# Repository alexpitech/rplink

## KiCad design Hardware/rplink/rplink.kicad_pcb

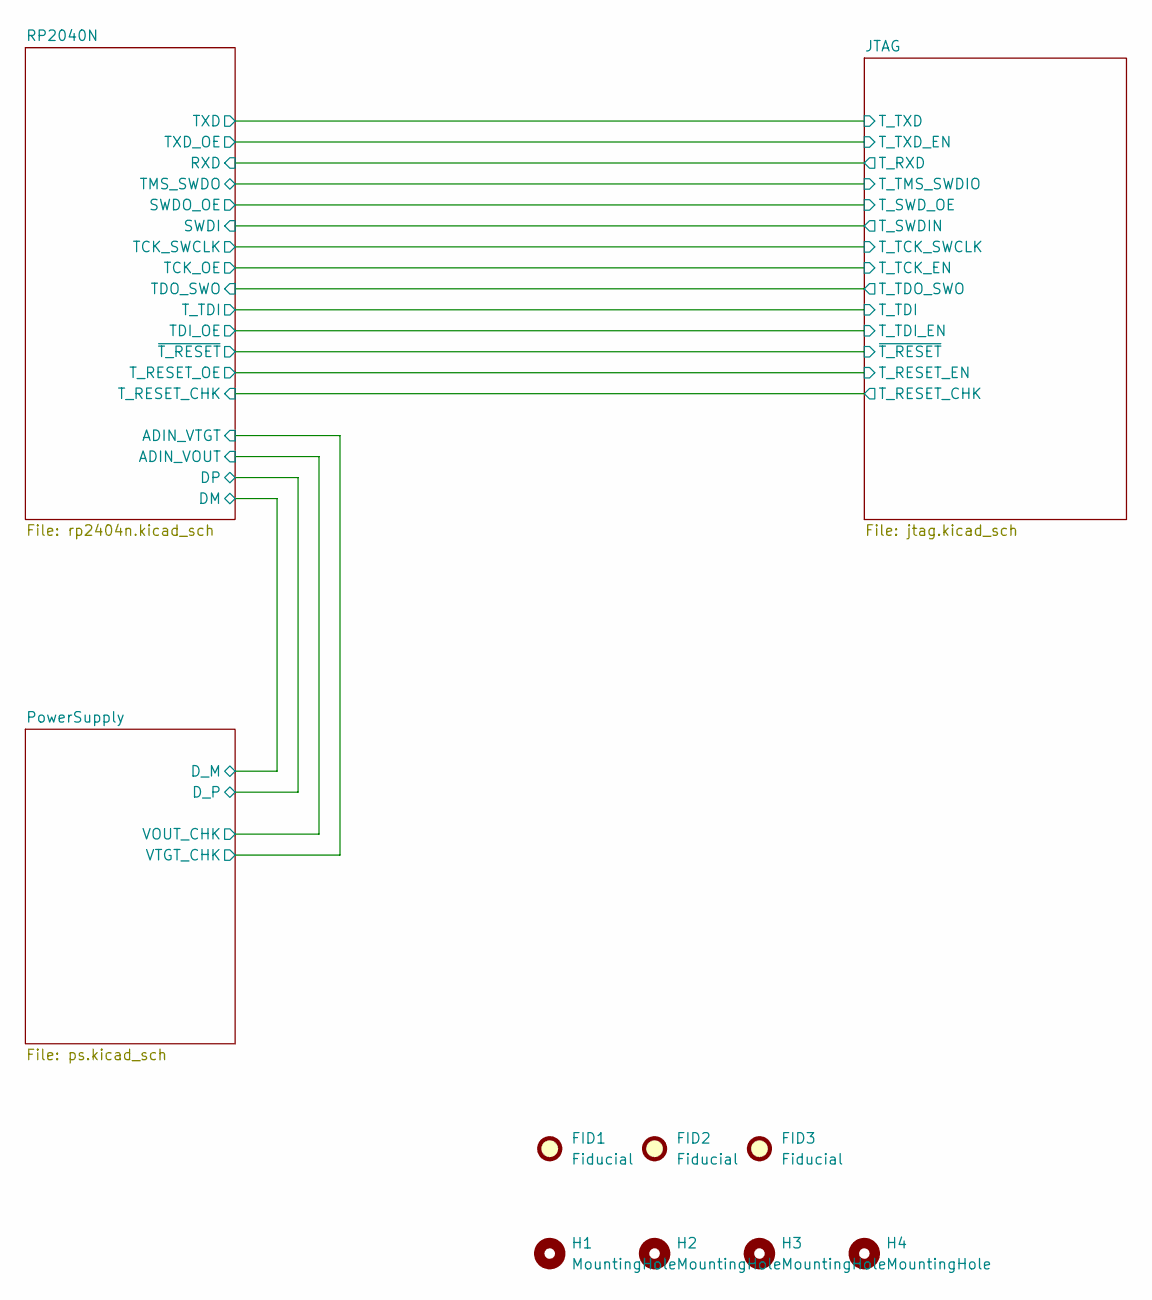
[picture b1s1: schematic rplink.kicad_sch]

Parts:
FID1, FID2, FID3: Fiducial; Fiducial_0.5mm_Mask1.5mm
H1, H2, H3, H4: MountingHole; MountingHole_3.2mm_M3

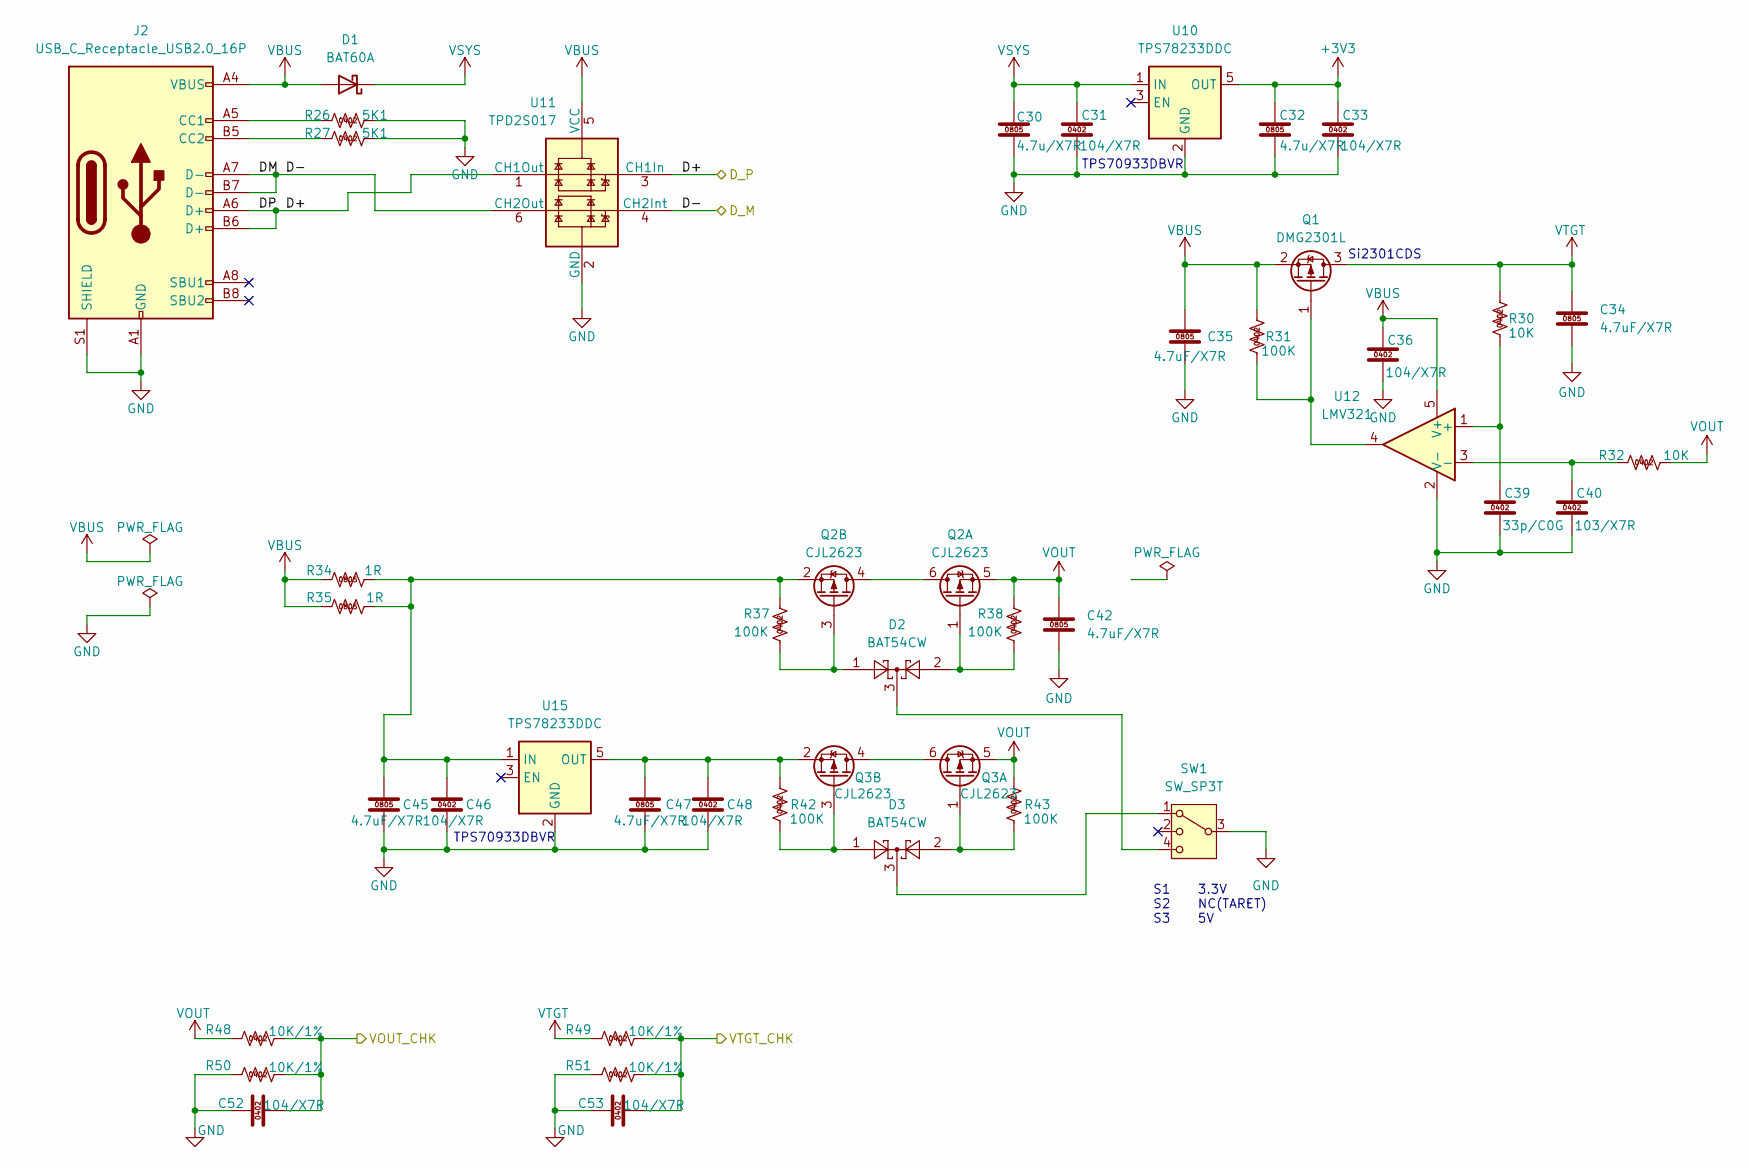
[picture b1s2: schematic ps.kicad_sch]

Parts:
C30, C32: 4.7u/X7R; C_0805_2012Metric
C31, C33, C36, C46, C48, C52, C53: 104/X7R; C_0402_1005Metric
C34, C35, C42, C45, C47: 4.7uF/X7R; C_0805_2012Metric
C39: 33p/C0G; C_0402_1005Metric
C40: 103/X7R; C_0402_1005Metric
D1: BAT60A; D_SOD-323
D2, D3: BAT54CW; SOT-323_SC-70
J2: USB_C_Receptacle_USB2.0_16P
Q1: DMG2301L; SOT-23
Q2, Q3: CJL2623; SOT-23-6
R26, R27: 5K1; R_0402_1005Metric
R30, R32: 10K; R_0402_1005Metric
R31, R37, R38, R42, R43: 100K; R_0402_1005Metric
R34, R35: 1R; R_0805_2012Metric
R48, R49, R50, R51: 10K/1%; R_0402_1005Metric
SW1: SW_SP3T; SW_SP3T_PCM13
U10, U15: TPS78233DDC; SOT-23-5
U11: TPD2S017; SOT-23-6
U12: LMV321; SOT-23-5

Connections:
+3V3: C32.1, C33.1, U10.5 (OUT); also elsewhere on the board
/PowerSupply/D+: J2.A6 (D+), J2.B6 (D+), U11.1 (CH1Out), U11.3 (CH1In); also elsewhere on the board
/PowerSupply/D-: J2.A7 (D-), J2.B7 (D-), U11.4 (CH2Int), U11.6 (CH2Out); also elsewhere on the board
/PowerSupply/VOUT_CHK: C52.2, R48.2, R50.2; also elsewhere on the board
/PowerSupply/VTGT_CHK: C53.2, R49.2, R51.2; also elsewhere on the board
GND: C30.2, C31.2, C32.2, C33.2, C34.2, C35.2, C36.2, C39.2, C40.2, C42.2, C45.2, C46.2, C47.2, C48.2, C52.1, C53.1, J2.A1 (GND), J2.A12 (GND), J2.B1 (GND), J2.B12 (GND), J2.S1 (SHIELD), R26.2, R27.2, R50.1, R51.1, SW1.3, U10.2 (GND), U10.4 (GND), U11.2 (GND), U12.2 (V-), U15.2 (GND), U15.4 (GND); also elsewhere on the board
unnamed: D2.3, SW1.4
unnamed: D3.3, SW1.1
unnamed: J2.A5 (CC1), R26.1
unnamed: J2.B5 (CC2), R27.1
unnamed: Q1.1 (G), R31.1, U12.4
unnamed: Q2.4 (D), Q2.6 (D)
unnamed: D2.2, Q2.1 (G), R38.1
unnamed: D2.1, Q2.3 (G), R37.1
unnamed: C45.1, C46.1, Q2.2 (S), R34.2, R35.2, R37.2, U15.1 (IN)
unnamed: Q3.4 (D), Q3.6 (D)
unnamed: D3.2, Q3.1 (G), R43.1
unnamed: D3.1, Q3.3 (G), R42.1
unnamed: C47.1, C48.1, Q3.2 (S), R42.2, U15.5 (OUT)
unnamed: C39.1, R30.1, U12.1 (+)
unnamed: C40.1, R32.1, U12.3 (-)
VBUS: C35.1, C36.1, D1.2 (A), J2.A4 (VBUS), J2.A9 (VBUS), J2.B4 (VBUS), J2.B9 (VBUS), Q1.2 (S), R31.2, R34.1, R35.1, U11.5 (VCC), U12.5 (V+)
VOUT: C42.1, Q2.5 (S), Q3.5 (S), R32.2, R38.2, R43.2, R48.1; also elsewhere on the board
VSYS: C30.1, C31.1, D1.1 (K), U10.1 (IN)
VTGT: C34.1, Q1.3 (D), R30.2, R49.1; also elsewhere on the board

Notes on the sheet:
Si2301CDS
TPS70933DBVR
S1 3.3V S2 NC(TARET) S3 5V

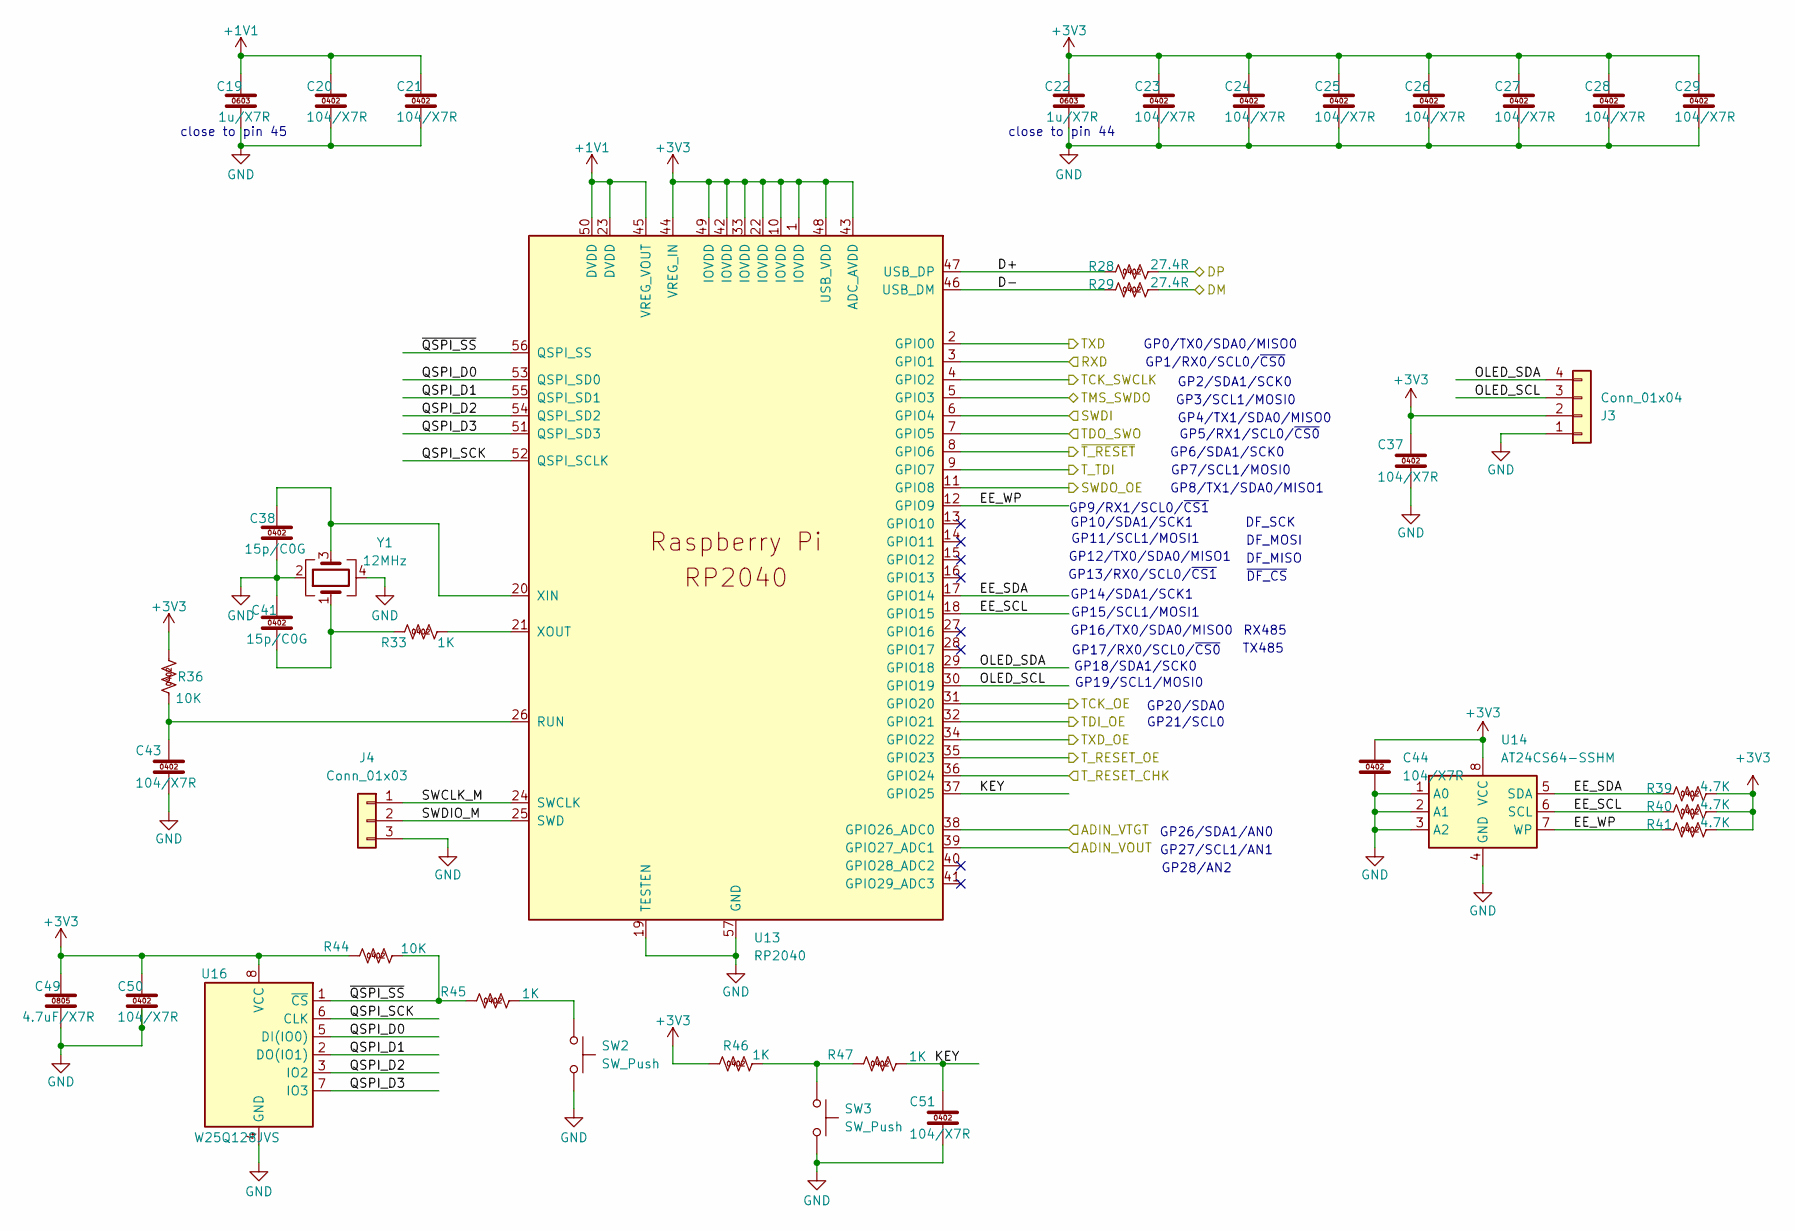
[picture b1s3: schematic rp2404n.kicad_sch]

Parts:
C19, C22: 1u/X7R; C_0603_1608Metric
C20, C21, C23, C24, C25, C26, C27, C28, C29, C37, C43, C44, C50, C51: 104/X7R; C_0402_1005Metric
C38, C41: 15p/C0G; C_0402_1005Metric
C49: 4.7uF/X7R; C_0805_2012Metric
J3: Conn_01x04; PinHeader_1x04_P2.54mm_Vertical
J4: Conn_01x03; PinHeader_1x03_P2.54mm_Vertical
R28, R29: 27.4R; R_0402_1005Metric
R33, R45, R46, R47: 1K; R_0402_1005Metric
R36, R44: 10K; R_0402_1005Metric
R39, R40, R41: 4.7K; R_0402_1005Metric
SW2: SW_Push; SW_Push_1P1T-MP_NO_Horizontal_Alps_SKRTLAE010
SW3: SW_Push; SW_Push_1P1T_NO_CK_KMR2
U13: RP2040; RP2040-QFN-56
U14: AT24CS64-SSHM; SOIC-8_3.9x4.9mm_P1.27mm
U16: W25Q128JVS; SOIC-8_5.23x5.23mm_P1.27mm
Y1: 12MHz; Crystal_SMD_WE_CFPX-180-4Pin_3.2x2.5mm

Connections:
+1V1: C19.1, C20.1, C21.1, U13.23 (DVDD), U13.45 (VREG_VOUT), U13.50 (DVDD)
+3V3: C22.1, C23.1, C24.1, C25.1, C26.1, C27.1, C28.1, C29.1, C37.1, C44.1, C49.1, C50.1, J3.2, R36.2, R39.2, R40.2, R41.2, R44.1, R46.1, U13.1 (IOVDD), U13.10 (IOVDD), U13.22 (IOVDD), U13.33 (IOVDD), U13.42 (IOVDD), U13.43 (ADC_AVDD), U13.44 (VREG_IN), U13.48 (USB_VDD), U13.49 (IOVDD), U14.8 (VCC), U16.8 (VCC); also elsewhere on the board
/JTAG/T_RESET_CHK: U13.36 (GPIO24); also elsewhere on the board
/JTAG/T_RESET_EN: U13.35 (GPIO23); also elsewhere on the board
/JTAG/T_RXD: U13.3 (GPIO1); also elsewhere on the board
/JTAG/T_SWDIN: U13.6 (GPIO4); also elsewhere on the board
/JTAG/T_SWD_OE: U13.11 (GPIO8); also elsewhere on the board
/JTAG/T_TCK_EN: U13.31 (GPIO20); also elsewhere on the board
/JTAG/T_TCK_SWCLK: U13.4 (GPIO2); also elsewhere on the board
/JTAG/T_TDI: U13.9 (GPIO7); also elsewhere on the board
/JTAG/T_TDI_EN: U13.32 (GPIO21); also elsewhere on the board
/JTAG/T_TDO_SWO: U13.7 (GPIO5); also elsewhere on the board
/JTAG/T_TMS_SWDIO: U13.5 (GPIO3); also elsewhere on the board
/JTAG/T_TXD: U13.2 (GPIO0); also elsewhere on the board
/JTAG/T_TXD_EN: U13.34 (GPIO22); also elsewhere on the board
/JTAG/~T_RESET: U13.8 (GPIO6); also elsewhere on the board
/PowerSupply/D+: R28.2; also elsewhere on the board
/PowerSupply/D-: R29.2; also elsewhere on the board
/PowerSupply/VOUT_CHK: U13.39 (GPIO27_ADC1); also elsewhere on the board
/PowerSupply/VTGT_CHK: U13.38 (GPIO26_ADC0); also elsewhere on the board
/RP2040N/D+: R28.1, U13.47 (USB_DP)
/RP2040N/D-: R29.1, U13.46 (USB_DM)
/RP2040N/EE_SCL: R40.1, U13.18 (GPIO15), U14.6 (SCL)
/RP2040N/EE_SDA: R39.1, U13.17 (GPIO14), U14.5 (SDA)
/RP2040N/EE_WP: R41.1, U13.12 (GPIO9), U14.7 (WP)
/RP2040N/KEY: C51.1, R47.2, U13.37 (GPIO25)
/RP2040N/OLED_SCL: J3.3, U13.30 (GPIO19)
/RP2040N/OLED_SDA: J3.4, U13.29 (GPIO18)
/RP2040N/QSPI_D0: U13.53 (QSPI_SD0), U16.5 (DI(IO0))
/RP2040N/QSPI_D1: U13.55 (QSPI_SD1), U16.2 (DO(IO1))
/RP2040N/QSPI_D2: U13.54 (QSPI_SD2), U16.3 (IO2)
/RP2040N/QSPI_D3: U13.51 (QSPI_SD3), U16.7 (IO3)
/RP2040N/QSPI_SCK: U13.52 (QSPI_SCLK), U16.6 (CLK)
/RP2040N/SWCLK_M: J4.1, U13.24 (SWCLK)
/RP2040N/SWDIO_M: J4.2, U13.25 (SWD)
/RP2040N/~QSPI_SS: R44.2, R45.1, U13.56 (QSPI_SS), U16.1 (~CS)
GND: C19.2, C20.2, C21.2, C22.2, C23.2, C24.2, C25.2, C26.2, C27.2, C28.2, C29.2, C37.2, C38.1, C41.2, C43.2, C44.2, C49.2, C50.2, C51.2, J3.1, J4.3, SW2.2, SW3.2, U13.19 (TESTEN), U13.57 (GND), U14.1 (A0), U14.2 (A1), U14.3 (A2), U14.4 (GND), U16.4 (GND), Y1.2, Y1.4; also elsewhere on the board
unnamed: C41.1, R33.1, Y1.1
unnamed: R45.2, SW2.1
unnamed: R46.2, R47.1, SW3.1
unnamed: C43.1, R36.1, U13.26 (RUN)
unnamed: C38.2, U13.20 (XIN), Y1.3
unnamed: R33.2, U13.21 (XOUT)

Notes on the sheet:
GP14/SDA1/SCK1
GP26/SDA1/AN0
TX485
~{DF_CS}
GP8/TX1/SDA0/MISO1
GP27/SCL1/AN1
GP0/TX0/SDA0/MISO0
GP15/SCL1/MOSI1
GP13/RX0/SCL0/~{CS1}
GP3/SCL1/MOSI0
DF_SCK
GP4/TX1/SDA0/MISO0
GP12/TX0/SDA0/MISO1
GP16/TX0/SDA0/MISO0
GP19/SCL1/MOSI0
RX485
GP18/SDA1/SCK0
close to pin 44
DF_MISO
GP1/RX0/SCL0/~{CS0}
GP2/SDA1/SCK0
close to pin 45
GP5/RX1/SCL0/~{CS0}
GP10/SDA1/SCK1
GP7/SCL1/MOSI0
GP6/SDA1/SCK0
GP20/SDA0
GP11/SCL1/MOSI1
DF_MOSI
GP17/RX0/SCL0/~{CS0}
GP9/RX1/SCL0/~{CS1}
GP28/AN2
GP21/SCL0

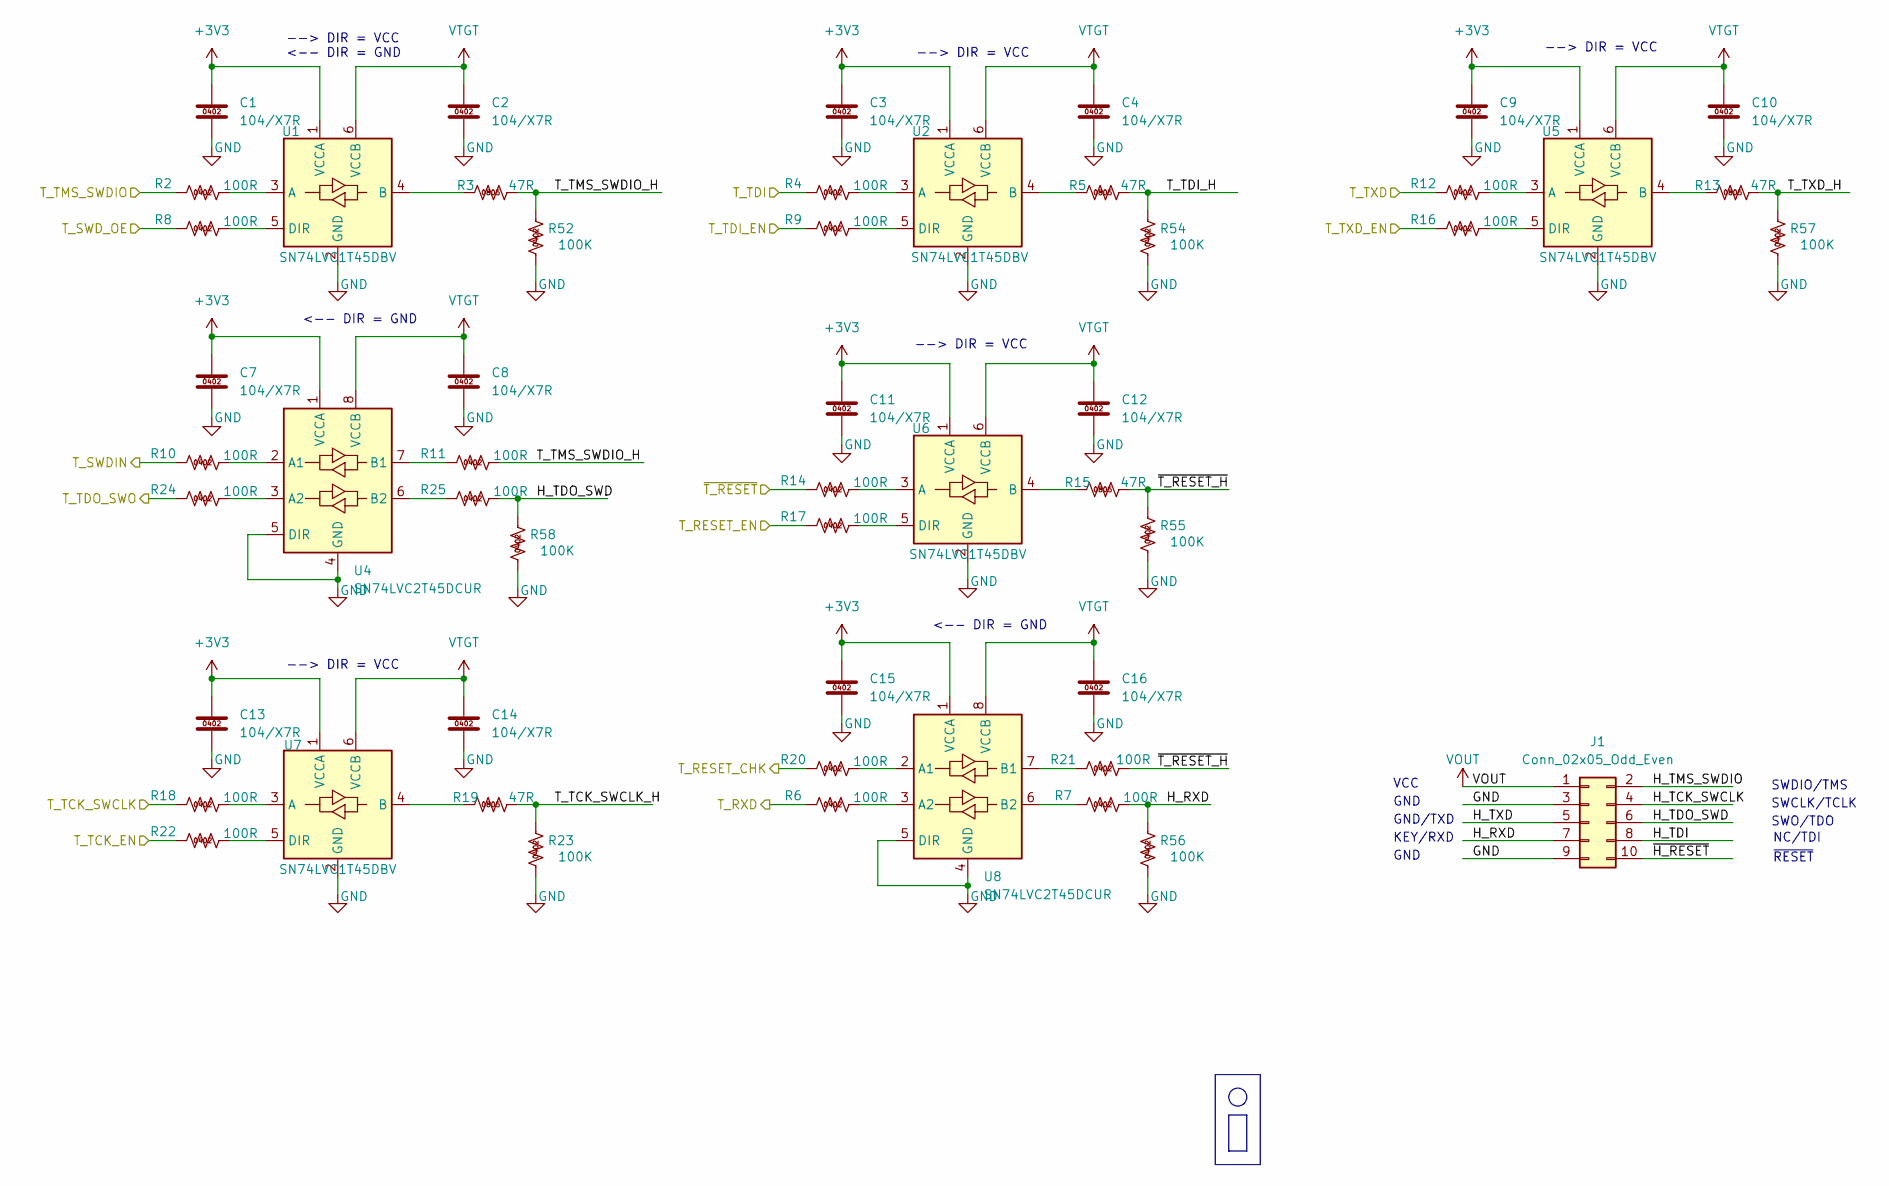
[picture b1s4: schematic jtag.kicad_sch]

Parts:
C1, C2, C3, C4, C7, C8, C9, C10, C11, C12, C13, C14, C15, C16: 104/X7R; C_0402_1005Metric
J1: Conn_02x05_Odd_Even; PinHeader_2x05_P2.54mm_Horizontal
R2, R4, R6, R7, R8, R9, R10, R11, R12, R14, R16, R17, R18, R20, R21, R22, R24, R25: 100R; R_0402_1005Metric
R3, R5, R13, R15, R19: 47R; R_0805_2012Metric
R23, R52, R54, R55, R56, R57, R58: 100K; R_0402_1005Metric
U1, U2, U5, U6, U7: SN74LVC1T45DBV; SOT-363_SC-70-6_Handsoldering
U4, U8: SN74LVC2T45DCUR; VSSOP-8_2.3x2mm_P0.5mm

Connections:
+3V3: C1.1, C3.1, C7.1, C9.1, C11.1, C13.1, C15.1, U1.1 (VCCA), U2.1 (VCCA), U4.1 (VCCA), U5.1 (VCCA), U6.1 (VCCA), U7.1 (VCCA), U8.1 (VCCA); also elsewhere on the board
/JTAG/H_RXD: J1.7, R7.2, R56.2
/JTAG/H_TCK_SWCLK: J1.4
/JTAG/H_TDI: J1.8
/JTAG/H_TDO_SWD: J1.6, R25.2, R58.2
/JTAG/H_TMS_SWDIO: J1.2
/JTAG/H_TXD: J1.5
/JTAG/T_RESET_CHK: R20.1; also elsewhere on the board
/JTAG/T_RESET_EN: R17.1; also elsewhere on the board
/JTAG/T_RXD: R6.1; also elsewhere on the board
/JTAG/T_SWDIN: R10.1; also elsewhere on the board
/JTAG/T_SWD_OE: R8.1; also elsewhere on the board
/JTAG/T_TCK_EN: R22.1; also elsewhere on the board
/JTAG/T_TCK_SWCLK: R18.1; also elsewhere on the board
/JTAG/T_TCK_SWCLK_H: R19.2, R23.2
/JTAG/T_TDI: R4.1; also elsewhere on the board
/JTAG/T_TDI_EN: R9.1; also elsewhere on the board
/JTAG/T_TDI_H: R5.2, R54.2
/JTAG/T_TDO_SWO: R24.1; also elsewhere on the board
/JTAG/T_TMS_SWDIO: R2.1; also elsewhere on the board
/JTAG/T_TMS_SWDIO_H: R3.2, R11.2, R52.2
/JTAG/T_TXD: R12.1; also elsewhere on the board
/JTAG/T_TXD_EN: R16.1; also elsewhere on the board
/JTAG/T_TXD_H: R13.2, R57.2
/JTAG/~H_RESET: J1.10
/JTAG/~T_RESET_H: R15.2, R21.2, R55.2
/JTAG/~T_RESET: R14.1; also elsewhere on the board
GND: C1.2, C2.2, C3.2, C4.2, C7.2, C8.2, C9.2, C10.2, C11.2, C12.2, C13.2, C14.2, C15.2, C16.2, J1.3, J1.9, R23.1, R52.1, R54.1, R55.1, R56.1, R57.1, R58.1, U1.2 (GND), U2.2 (GND), U4.4 (GND), U4.5 (DIR), U5.2 (GND), U6.2 (GND), U7.2 (GND), U8.4 (GND), U8.5 (DIR); also elsewhere on the board
unnamed: R2.2, U1.3 (A)
unnamed: R3.1, U1.4 (B)
unnamed: R8.2, U1.5 (DIR)
unnamed: R4.2, U2.3 (A)
unnamed: R5.1, U2.4 (B)
unnamed: R9.2, U2.5 (DIR)
unnamed: R10.2, U4.2 (A1)
unnamed: R24.2, U4.3 (A2)
unnamed: R11.1, U4.7 (B1)
unnamed: R25.1, U4.6 (B2)
unnamed: R12.2, U5.3 (A)
unnamed: R13.1, U5.4 (B)
unnamed: R16.2, U5.5 (DIR)
unnamed: R14.2, U6.3 (A)
unnamed: R15.1, U6.4 (B)
unnamed: R17.2, U6.5 (DIR)
unnamed: R18.2, U7.3 (A)
unnamed: R19.1, U7.4 (B)
unnamed: R22.2, U7.5 (DIR)
unnamed: R20.2, U8.2 (A1)
unnamed: R6.2, U8.3 (A2)
unnamed: R21.1, U8.7 (B1)
unnamed: R7.1, U8.6 (B2)
VOUT: J1.1; also elsewhere on the board
VTGT: C2.1, C4.1, C8.1, C10.1, C12.1, C14.1, C16.1, U1.6 (VCCB), U2.6 (VCCB), U4.8 (VCCB), U5.6 (VCCB), U6.6 (VCCB), U7.6 (VCCB), U8.8 (VCCB); also elsewhere on the board

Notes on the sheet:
SWDIO/TMS
GND
--> DIR = VCC
SWCLK/TCLK
NC/TDI
SWO/TDO
<-- DIR = GND
--> DIR = VCC <-- DIR = GND
~{RESET}
GND/TXD
KEY/RXD
VCC

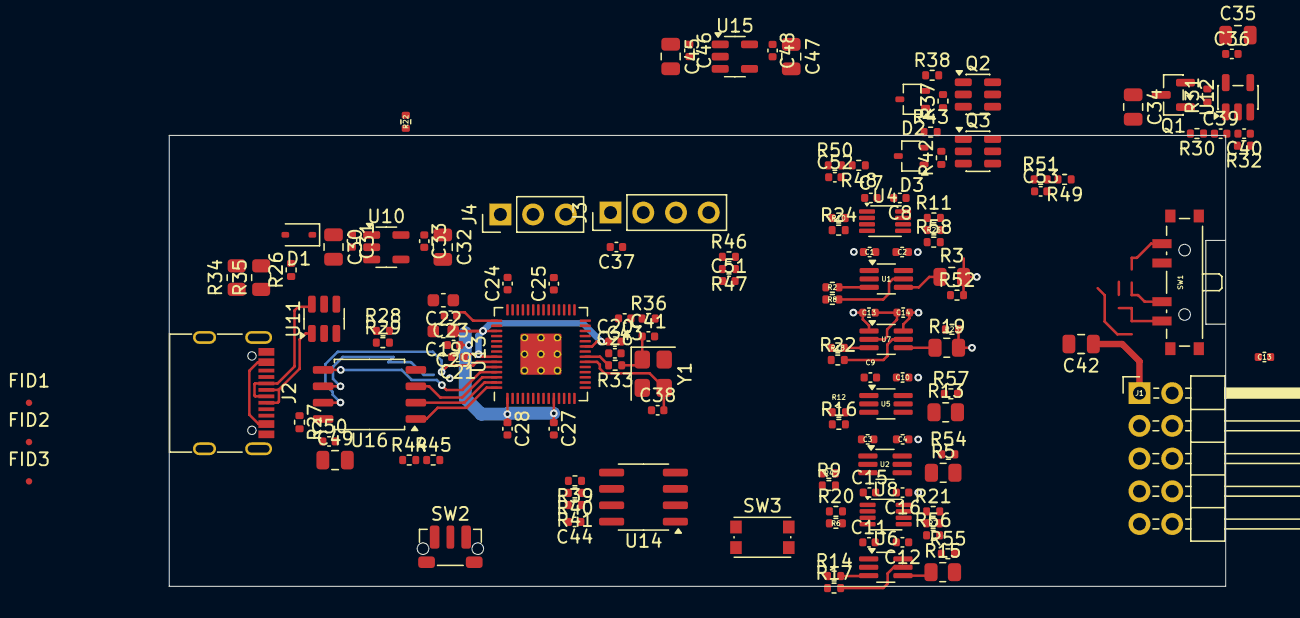
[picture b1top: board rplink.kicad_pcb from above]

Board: 2 copper layers, 82.0 x 35.0 mm, 142 parts (0 on the bottom side), 92 nets.

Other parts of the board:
C13#2: 104/X7R; C_0402_1005Metric
R22#2: 4.7K; R_0402_1005Metric

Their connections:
+3V3: R22#2.2; also elsewhere on the board
GND: C13#2.1; also elsewhere on the board

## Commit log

2024-06-09 Developing
2024-06-09 add lib
2026-05-28 rev 0.1
2026-05-29 完成初步布局
